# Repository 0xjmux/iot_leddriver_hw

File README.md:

# Spotify Neopixel Visualizer Hardware
Simple and compact ESP32-based WS2812B LED Strip Driver.   

<!-- * Board firmware (in progress, not yet published) will be eventually available at [iot_leddriver_sw](https://github.com/0xjmux/iot_leddriver_sw). -->
* Origianlly planned to design my own firmware to integrate with the Spotify API Directly; but eventually switched to the much more featured combination of WLED + LEDFx. 
* Compatible with the popular [WLED](https://github.com/Aircoookie/WLED) firmware: just change the LED data pin to `GPIO21`. 
* (See [DEVELOPMENT-NOTES.md](DEVELOPMENT-NOTES.md) for full pinout and other information).

> [!WARNING]
> This was my first real PCB design, and I've improved a lot since I completed it. Take it (especially <=v2.2) with a grain of salt. 
 
### Features
* ESP32 based for low-cost IoT Capability, can use either `ESP32-S2-SOLO` (single core, cheaper) or `ESP32-S3-WROOM` (dual core). 
* Programmable over USB C, with Tag-Connect JTAG header for full debug capability. 
* Two ways to attach LED strip, either via pin header or with a strain relief. 
* Board designed to drive a 5m 60LED/m WS2812B strip with safety marign (see [DEVELOPMENT-NOTES.md](DEVELOPMENT-NOTES.md))
* Entirely LCSC BOM, designed for both hand and machine assembly. Able to be assembled by JLCPCB with low-cost components (almost all basic component BOM).

##### Optional Features and Mounting
* Designed to also be capable of driving 12V strips like the WS2811; only modification needed is changing the 5V overvoltage protection diodes (`D1`&`D2`, PN `SMF5V0A`) to 12V diodes (like `SMF12A`s)
* M2 mounting holes, various test pads, and an emergency UART header on the bottom. 
* Includes I2C breakout for optional addition of SSD1306 OLED.
* MEMS Microphone can optionally be added for live sound reactivity. 

#### Update 1/2024 - Now with a 3D Printable case!
* Check out [case/](./case/) for the 3D printable case I designed! This is the result of my first design using CAD in a very long time, and while it has some things I would change now I think it's still probably better published than not. 
* A PDF drawing of the case with dimensions can be found [here](case/iot_leddriver_drawing_v0.5.pdf).

## Notes and Usage
* Schematic, BOM, Gerbers, and all other files needed for production and assembly can be found attached to the latest [release!](https://github.com/0xjmux/iot_leddriver_hw/releases/latest)
  * This includes an interactive HTML BOM, which makes hand assembly much easier. 
* View current layout and schematic live on [KiCanvas](https://kicanvas.org/?github=https%3A%2F%2Fgithub.com%2F0xjmux%2Fiot_leddriver_hw%2Ftree%2Fmain%2FPCB)

<p align="center">
  
<br>v2.1 showing LED strip standard JST connector connected to 5M WS2812B strip
</p>

## Versions
### V2.2 - QoL and Improvements for Production
* Mostly minor updates, to bring the board up to a more "production" ready state. Some modifications/fixes for small things found during manual assembly. 
* Power trace width from USB C port increased so short lengths of strip can be driven directly from USB.
* Traces cleaned up, PWR_LED can now be disconnected (if it's going to be deployed somewhere and the constant light is unwanted). USB_PWR jumpers removed. 
* BOM consolidation, some notes added to schematic, documentation improvements. 

### V2.1 - Hand Assembleable
* MCU originally selected for V2, the `ESP32-S2-MINI`, wasn't hand assemble-able; so it's been replaced with an `ESP32-S2-SOLO`. 
* Various small upgrades, including removal of non-necessary RC components, a mini UART header, and additional 5V power lines right next to the 2.1mm jack for strips with additional power wires. 
* The footprint and supporting components for a MEMS Microphone (`SPH0641LM4H-1`) added in case live sound reactivity is desired later on. 

### V2.0 - Complete redesign, now ESP32 Based
* Board upgraded to the `ESP32-S2-MINI-2-N4` for better compute capability, completely redesigned solely around the WS2812B.
* Most of the features listed above were introduced in this version.

---
### V1.0 Prototype
* [Link to v1.0 branch](https://github.com/0xjmux/iot_leddriver_hw/tree/v1.0)
* V1.0 was an IoT enabled LED strip driver using ESP8266 capable of using both WS2812B (Neopixel) and standard 5050 12V LED strips. Goal is to integrate with the spotify API to allow color changes in reaction to music. 
* V1 was never fully tested; right as v1.0 was ready my goal with the project shifted, and the ESP82666 just doesn't have enough compute for what I wanted to do. 
* If board will only be used in 5V (neopixel) mode, then the 3 `UMW30N06` Mosfets and 2 of the `MCP1416` mosfet drivers are not needed. Additionally, if the board will only be run in one mode then the unused 2.1mm jack does not need to be installed.

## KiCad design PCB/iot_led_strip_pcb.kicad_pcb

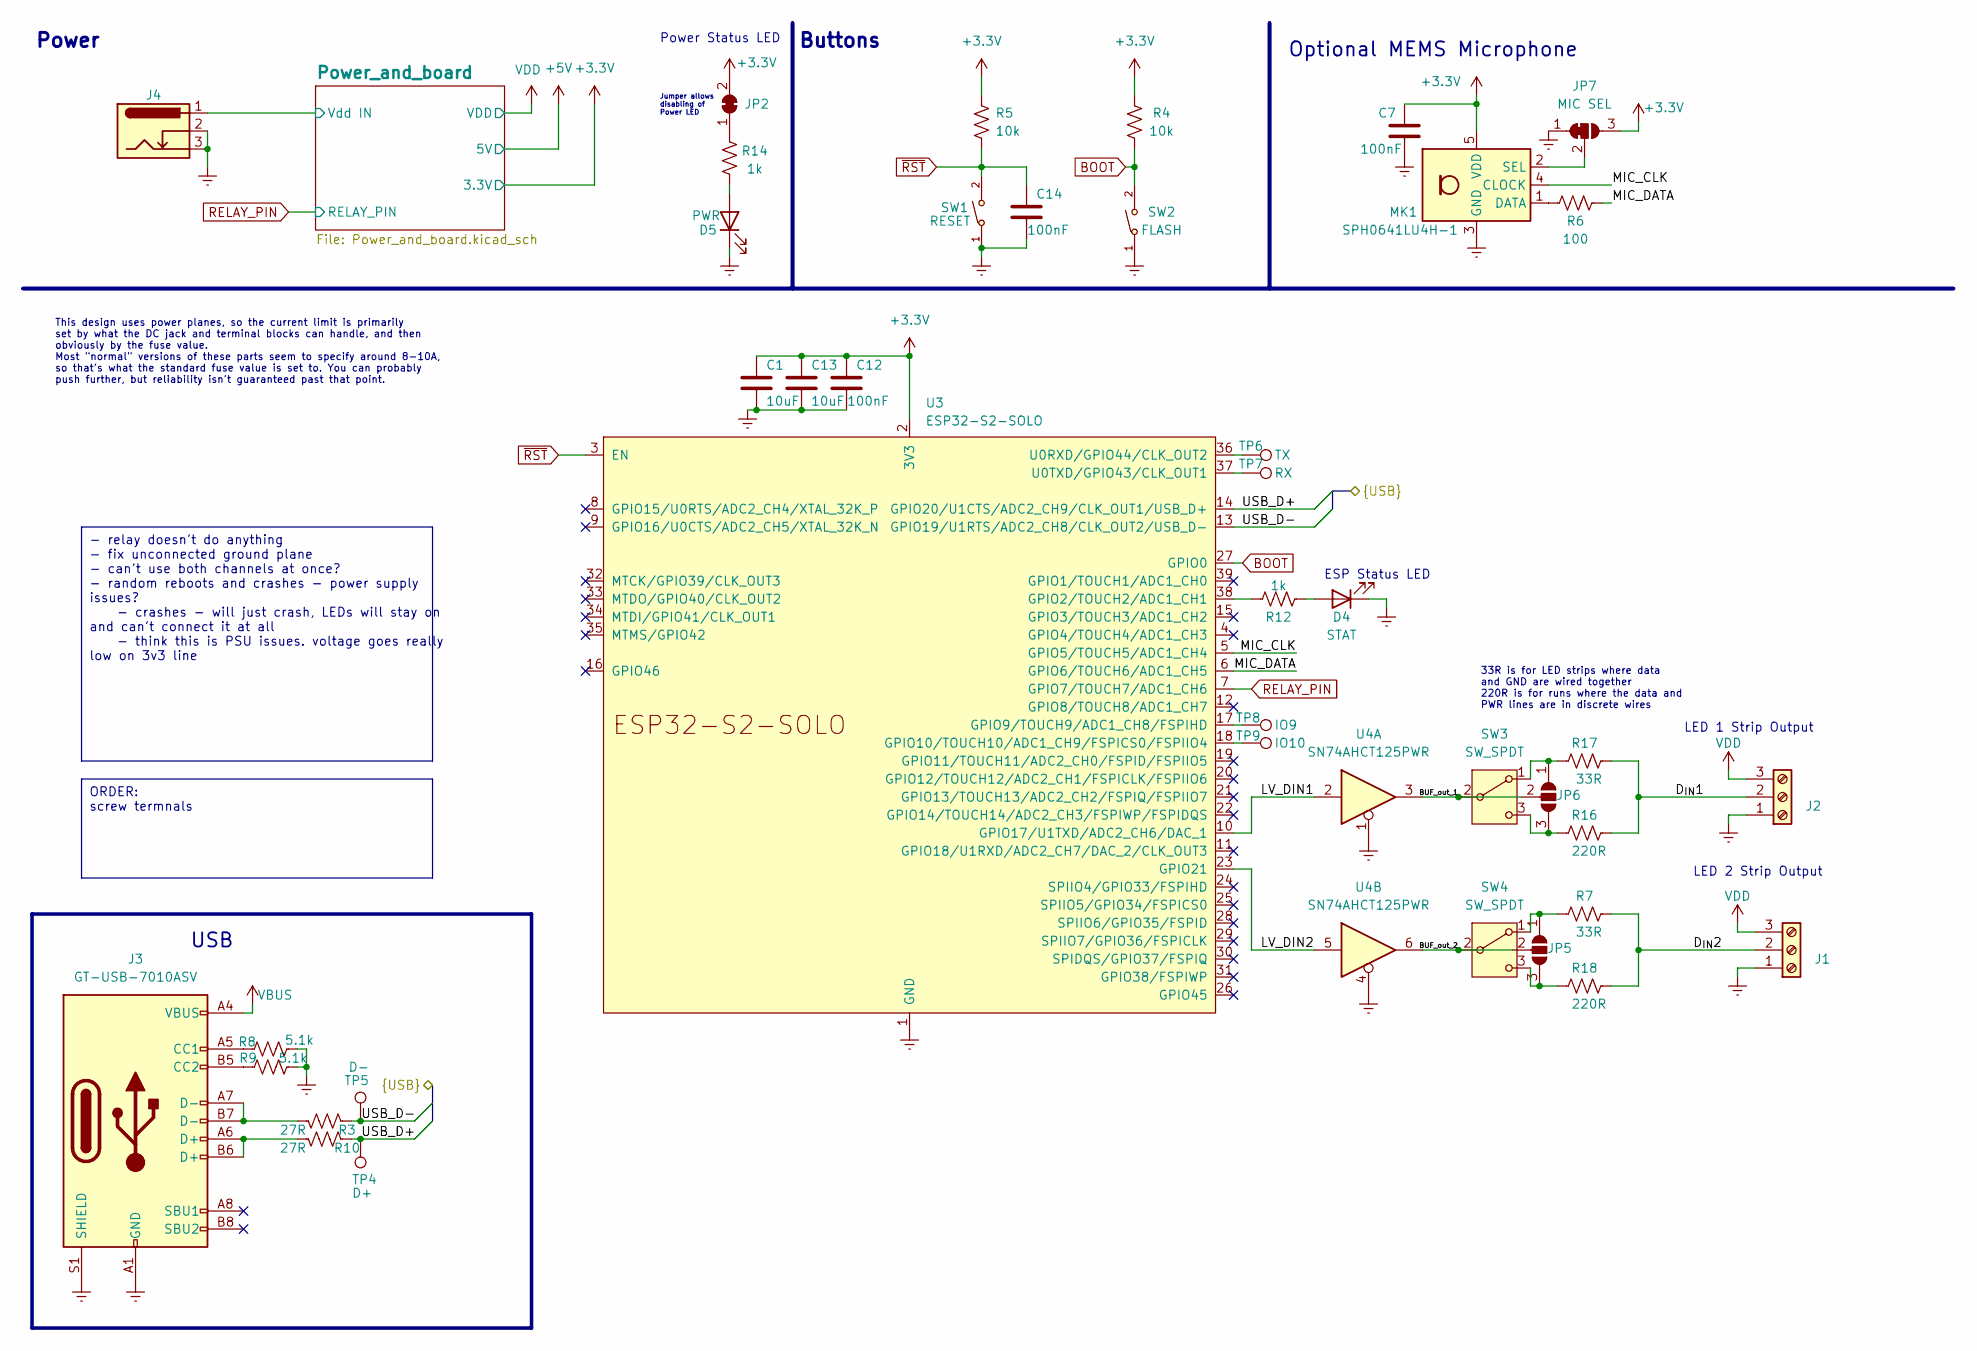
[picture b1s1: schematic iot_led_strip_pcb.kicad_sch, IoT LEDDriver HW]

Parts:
C1, C13: 10uF; C_0805_2012Metric_Pad1.18x1.45mm_HandSolder; LCSC C15850
C7, C12, C14: 100nF; C_0805_2012Metric_Pad1.18x1.45mm_HandSolder; LCSC C49678
D4: STAT; LED_0805_2012Metric_Pad1.15x1.40mm_HandSolder; LCSC C2297
D5: PWR; LED_0805_2012Metric_Pad1.15x1.40mm_HandSolder; LCSC C84256
J1, J2: Screw_Terminal_01x03; TerminalBlock_bornier-3_P5.08mm; LCSC C5188425
J3: GT-USB-7010ASV; USB-C-GT7010_FIXED; LCSC C2988369
J4: Barrel_Jack_Switch_Pin3Ring; BarrelJack_Wuerth_6941xx301002
JP2: PWR_LED_BRIDGE; SolderJumper-2_P1.3mm_Bridged_RoundedPad1.0x1.5mm
JP5, JP6: SolderJumper_3_Open; SolderJumper-3_P1.3mm_Open_Pad1.0x1.5mm
JP7: MIC SEL; SolderJumper-3_P1.3mm_Bridged12_RoundedPad1.0x1.5mm
MK1: SPH0641LU4H-1; Knowles_LGA-5_3.5x2.65mm; LCSC C5454543
R3, R10: 27R; R_0805_2012Metric_Pad1.20x1.40mm_HandSolder; LCSC C17594
R4, R5: 10k; R_0805_2012Metric_Pad1.20x1.40mm_HandSolder; LCSC C17414
R6: 100; R_0805_2012Metric_Pad1.20x1.40mm_HandSolder; LCSC C17408
R7, R17: 33R; R_0805_2012Metric_Pad1.20x1.40mm_HandSolder; LCSC C17634
R8, R9: 5.1k; R_0805_2012Metric_Pad1.20x1.40mm_HandSolder; LCSC C27834
R12, R14: 1k; R_0805_2012Metric_Pad1.20x1.40mm_HandSolder; LCSC C17513
R16, R18: 220R; R_0805_2012Metric_Pad1.20x1.40mm_HandSolder; LCSC C17557
SW1: RESET; SW_SPST_TL3342; LCSC C318884
SW2: FLASH; SW_SPST_TL3342; LCSC C318884
SW3, SW4: SW_SPDT; SW_SPDT_PCM12; LCSC C319020
TP4: D+; TestPoint_Pad_D1.5mm
TP5: D-; TestPoint_Pad_D1.5mm
TP6: TX; TestPoint_Pad_D1.5mm
TP7: RX; TestPoint_Pad_D1.5mm
TP8: IO9; TestPoint_Pad_D1.5mm
TP9: IO10; TestPoint_Pad_D1.5mm
U3: ESP32-S2-SOLO; LCSC C3040594
U4: SN74AHCT125PWR; TSSOP-14_4.4x5mm_P0.65mm; LCSC C36365

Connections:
+3.3V: C1.1, C7.1, C12.1, C13.1, JP2.2 (B), JP7.3 (B), MK1.5 (VDD), R4.2, R5.1, U3.2 (3V3); also elsewhere on the board
/BUF_out_1: JP6.2 (C), SW3.2 (B), U4.3
/BUF_out_2: JP5.2 (C), SW4.2 (B), U4.6
/D_{IN}1: J2.2, R16.2, R17.2
/D_{IN}2: J1.2, R7.2, R18.2
/LV_DIN1: U3.10 (GPIO17/U1TXD/ADC2_CH6/DAC_1), U4.2
/LV_DIN2: U3.23 (GPIO21), U4.5
/MIC_CLK: MK1.4 (CLOCK), U3.5 (GPIO5/TOUCH5/ADC1_CH4)
/MIC_DATA: R6.1, U3.6 (GPIO6/TOUCH6/ADC1_CH5)
/Power_and_board/Vdd IN: J4.1; also elsewhere on the board
/USB_D+: R10.2, TP4.1, U3.14 (GPIO20/U1CTS/ADC2_CH9/CLK_OUT1/USB_D+)
/USB_D-: R3.2, TP5.1, U3.13 (GPIO19/U1RTS/ADC2_CH8/CLK_OUT2/USB_D-)
BOOT: R4.1, SW2.2, U3.27 (GPIO0)
Earth: C1.2, C7.2, C12.2, C13.2, C14.2, D4.1 (K), D5.1 (K), J1.1, J2.1, J3.A1 (GND), J3.A12 (GND), J3.B1 (GND), J3.B12 (GND), J3.S1 (SHIELD), J4.2, J4.3, JP7.1 (A), MK1.3 (GND), R8.2, R9.1, SW1.1, SW2.1, U3.1 (GND), U3.40 (GND), U3.41 (GND), U4.1, U4.4; also elsewhere on the board
unnamed: D4.2 (A), R12.1
unnamed: D5.2 (A), R14.1
unnamed: J3.A5 (CC1), R8.1
unnamed: J3.B5 (CC2), R9.2
unnamed: J3.A6 (D+), J3.B6 (D+), R10.1
unnamed: J3.A7 (D-), J3.B7 (D-), R3.1
unnamed: JP2.1 (A), R14.2
unnamed: JP5.1 (A), R7.1, SW4.1 (A)
unnamed: JP5.3 (B), R18.1, SW4.3 (C)
unnamed: JP6.1 (A), R17.1, SW3.1 (A)
unnamed: JP6.3 (B), R16.1, SW3.3 (C)
unnamed: JP7.2 (C), MK1.2 (SEL)
unnamed: MK1.1 (DATA), R6.2
unnamed: R12.2, U3.38 (GPIO2/TOUCH2/ADC1_CH1)
unnamed: TP8.1, U3.17 (GPIO9/TOUCH9/ADC1_CH8/FSPIHD)
unnamed: TP9.1, U3.18 (GPIO10/TOUCH10/ADC1_CH9/FSPICS0/FSPIIO4)
unnamed: TP6.1, U3.36 (U0RXD/GPIO44/CLK_OUT2)
unnamed: TP7.1, U3.37 (U0TXD/GPIO43/CLK_OUT1)
RELAY_PIN: U3.7 (GPIO7/TOUCH7/ADC1_CH6); also elsewhere on the board
VBUS: J3.A4 (VBUS), J3.A9 (VBUS), J3.B4 (VBUS), J3.B9 (VBUS); also elsewhere on the board
VDD: J1.3, J2.3; also elsewhere on the board
~RST: C14.1, R5.2, SW1.2, U3.3 (EN)

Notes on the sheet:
ORDER: screw termnals
- relay doesn't do anything - fix unconnected ground plane - can't use both channels at once? - random reboots and crashes - power supply issues? - crashes - will just crash, LEDs will stay on and can't connect it at all - think this is PSU issues. voltage goes really low on 3v3 line
Power
Buttons
Jumper allows disabling of Power LED
33R is for LED strips where data and GND are wired together 220R is for runs where the data and PWR lines are in discrete wires
This design uses power planes, so the current limit is primarily set by what the DC jack and terminal blocks can handle, and then obviously by the fuse value. Most "normal" versions of these parts seem to specify around 8-10A, so that's what the standard fuse value is set to. You can probably push 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
LED 2 Strip Output
LED 1 Strip Output
ESP Status LED
Power Status LED
USB
Optional MEMS Microphone

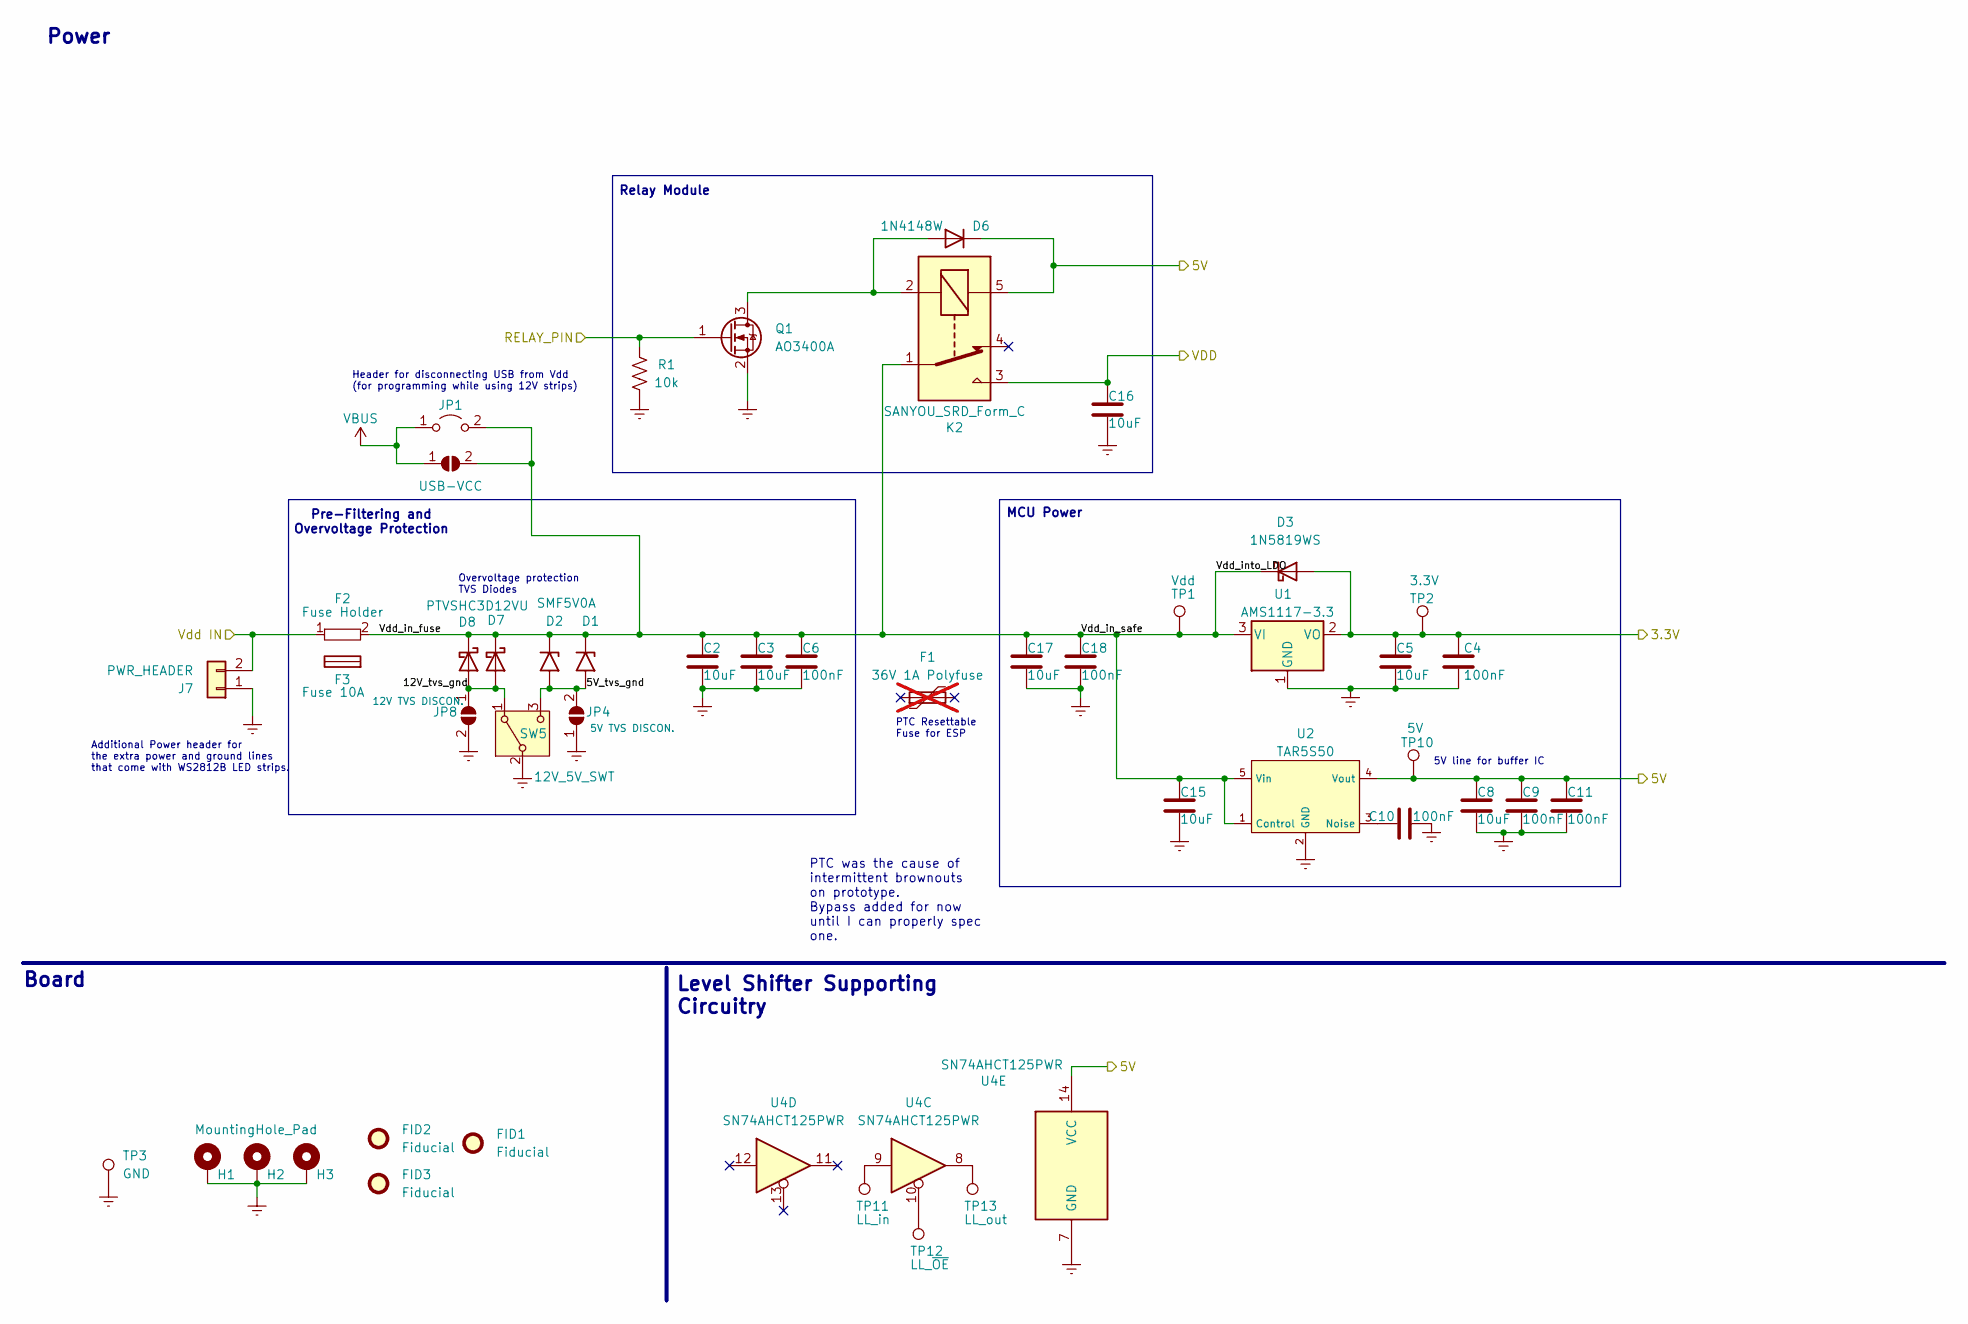
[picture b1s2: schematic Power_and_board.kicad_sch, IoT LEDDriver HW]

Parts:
C2, C3, C5, C8, C15, C16, C17: 10uF; C_0805_2012Metric_Pad1.18x1.45mm_HandSolder; LCSC C15850
C4, C6, C9, C10, C11, C18: 100nF; C_0805_2012Metric_Pad1.18x1.45mm_HandSolder; LCSC C49678
D1, D2: SMF5V0A; D_SMF; LCSC C1972946
D3: 1N5819WS; D_SOD-323_HandSoldering; LCSC C191023
D6: 1N4148W; D_SOD-123; LCSC C81598
D7, D8: PTVSHC3D12VU; D_SOD-323_HandSoldering; LCSC C169336
F1: 36V 1A Polyfuse; Fuse_1206_3216Metric_Pad1.42x1.75mm_HandSolder; LCSC C20616702; not fitted
F2: Fuse Holder; FUSE-TH_XF-505P; LCSC C843270
F3: Fuse 10A
FID1, FID2, FID3: Fiducial; Fiducial_0.5mm_Mask1mm
H1, H2, H3: MountingHole_Pad; MountingHole_2.2mm_M2_Pad_Via
J7: PWR_HEADER; SolderWire-0.5sqmm_1x02_P4.6mm_D0.9mm_OD2.1mm
JP1: USB-VDD; TestPoint_2Pads_Pitch2.54mm_Drill0.8mm
JP3: USB-VCC; SolderJumper-2_P1.3mm_Open_RoundedPad1.0x1.5mm
JP4: 5V TVS DISCON.; SolderJumper-2_P1.3mm_Open_RoundedPad1.0x1.5mm
JP8: 12V TVS DISCON.; SolderJumper-2_P1.3mm_Open_RoundedPad1.0x1.5mm
K2: SANYOU_SRD_Form_C; Relay_SPDT_SANYOU_SRD_Series_Form_C; LCSC C35449
Q1: AO3400A; SOT-23_Handsoldering; LCSC C20917
R1: 10k; R_0805_2012Metric_Pad1.20x1.40mm_HandSolder; LCSC C17414
SW5: 12V_5V_SWT; SW_SPDT_PCM12; LCSC C319020
TP1: Vdd; TestPoint_Pad_D1.5mm
TP2: 3.3V; TestPoint_Pad_D1.5mm
TP3: GND; TestPoint_Pad_D1.5mm
TP10: 5V; TestPoint_Pad_D1.5mm
TP11: LL_in; TestPoint_Pad_D1.0mm
TP12: LL_~{OE}; TestPoint_Pad_D1.0mm
TP13: LL_out; TestPoint_Pad_D1.0mm
U1: AMS1117-3.3; SOT-223-3_TabPin2; LCSC C6186
U2: TAR5S50; SSOP-5_L2.9-W1.6-P0.95-LS2.8-TL; LCSC C146354
U4: SN74AHCT125PWR; TSSOP-14_4.4x5mm_P0.65mm; LCSC C36365

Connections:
+3.3V: C4.1, C5.1, D3.2 (A), TP2.1, U1.2 (VO); also elsewhere on the board
+5V: C8.1, C9.1, C11.1, D6.1 (K), K2.5, TP10.1, U2.4 (Vout), U4.14 (VCC)
/Power_and_board/5V_tvs_gnd: D1.2 (A2), D2.2 (A2), JP4.2 (B), SW5.3 (C)
/Power_and_board/12V_tvs_gnd: D7.2 (A), D8.2 (A), JP8.1 (A), SW5.1 (A)
/Power_and_board/Vdd IN: F2.1, J7.2; also elsewhere on the board
/Power_and_board/Vdd_in_fuse: C2.1, C3.1, C6.1, C15.1, C17.1, C18.1, D1.1 (A1), D2.1 (A1), D3.1 (K), D7.1 (K), D8.1 (K), F2.2, JP1.2 (B), JP3.2 (B), K2.1, TP1.1, U1.3 (VI), U2.1 (Control), U2.5 (Vin)
Earth: C2.2, C3.2, C4.2, C5.2, C6.2, C8.2, C9.2, C10.2, C11.2, C15.2, C16.2, C17.2, C18.2, H1.1, H2.1, H3.1, J7.1, JP4.1 (A), JP8.2 (B), Q1.2 (S), R1.1, SW5.2 (B), TP3.1, U1.1 (GND), U2.2 (GND), U4.7 (GND); also elsewhere on the board
unnamed: D6.2 (A), K2.2, Q1.3 (D)
unnamed: TP11.1, U4.9
unnamed: TP12.1, U4.10
unnamed: TP13.1, U4.8
unnamed: C10.1, U2.3 (Noise)
RELAY_PIN: Q1.1 (G), R1.2; also elsewhere on the board
VBUS: JP1.1 (A), JP3.1 (A); also elsewhere on the board
VDD: C16.1, K2.3; also elsewhere on the board

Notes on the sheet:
PTC was the cause of intermittent brownouts on prototype. Bypass added for now until I can properly spec one.
5V line for buffer IC
Overvoltage protection TVS Diodes
Relay Module
MCU Power
Header for disconnecting USB from Vdd (for programming while using 12V strips)
Pre-Filtering and Overvoltage Protection
PTC Resettable Fuse for ESP
Board
Additional Power header for the extra power and ground lines that come with WS2812B LED strips.
Power
Level Shifter Supporting Circuitry

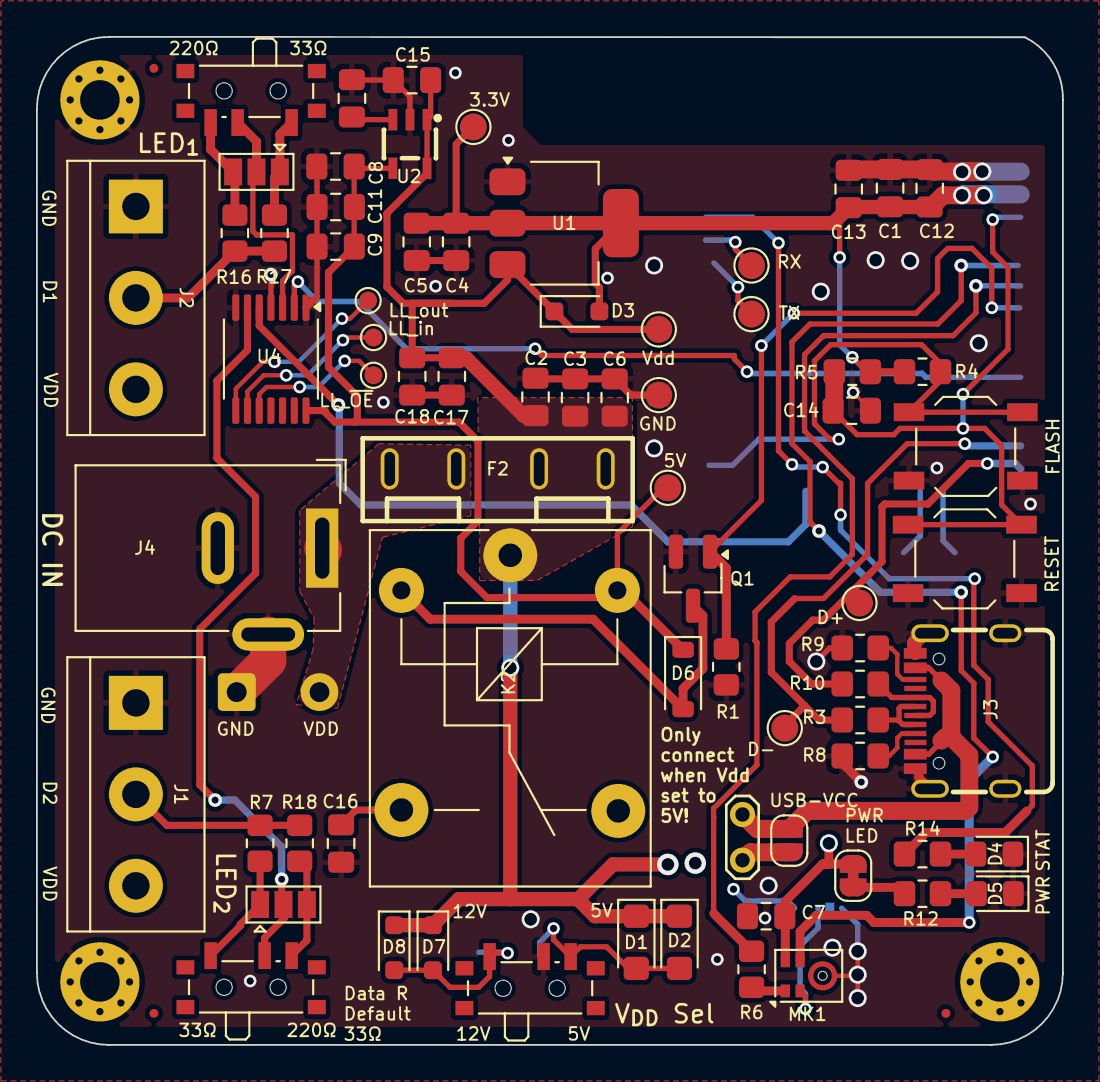
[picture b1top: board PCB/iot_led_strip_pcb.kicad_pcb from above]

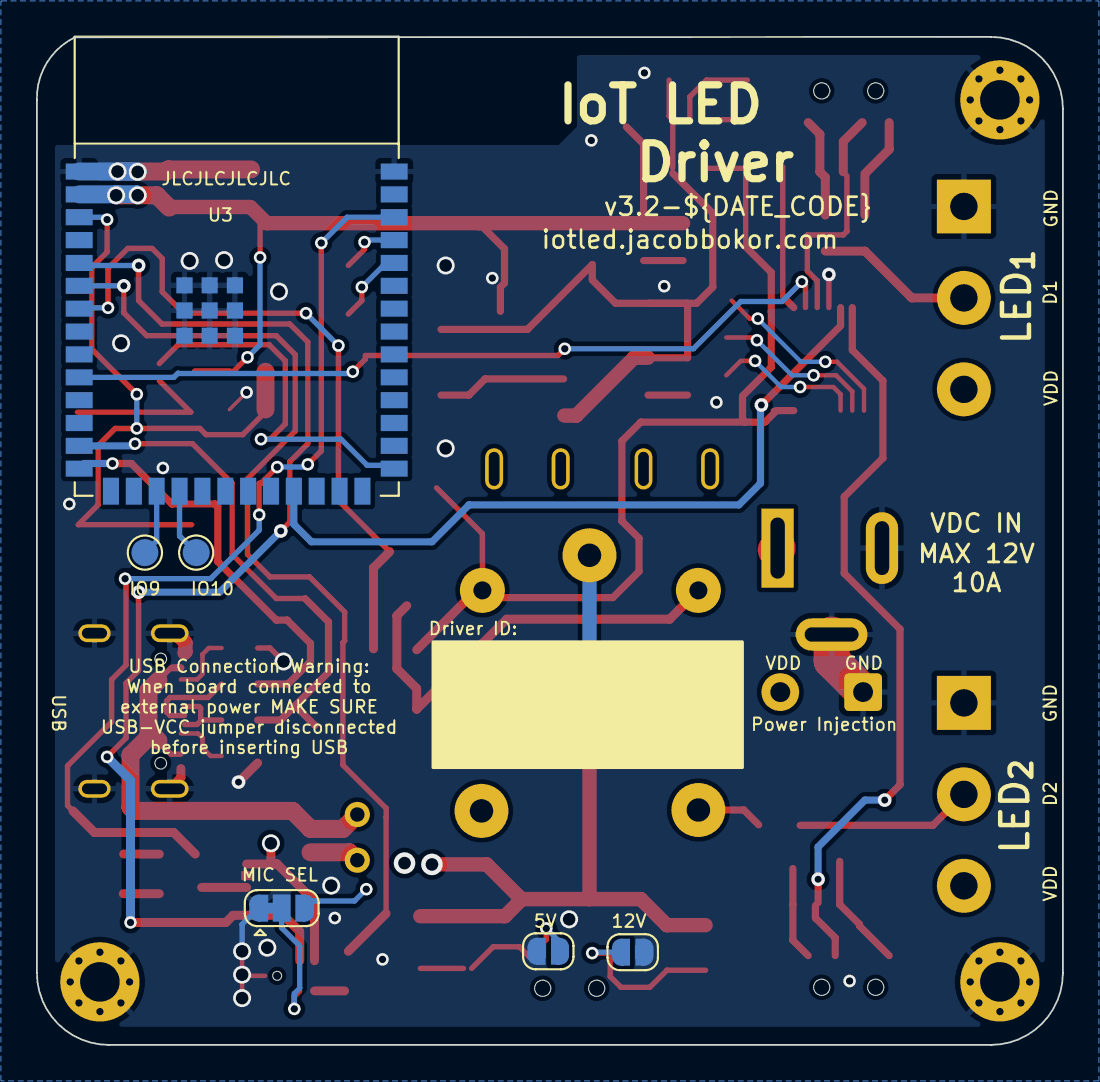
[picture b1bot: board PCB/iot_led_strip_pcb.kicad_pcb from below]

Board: 4 copper layers, 57.0 x 56.0 mm, 85 parts (6 on the bottom side), 45 nets.

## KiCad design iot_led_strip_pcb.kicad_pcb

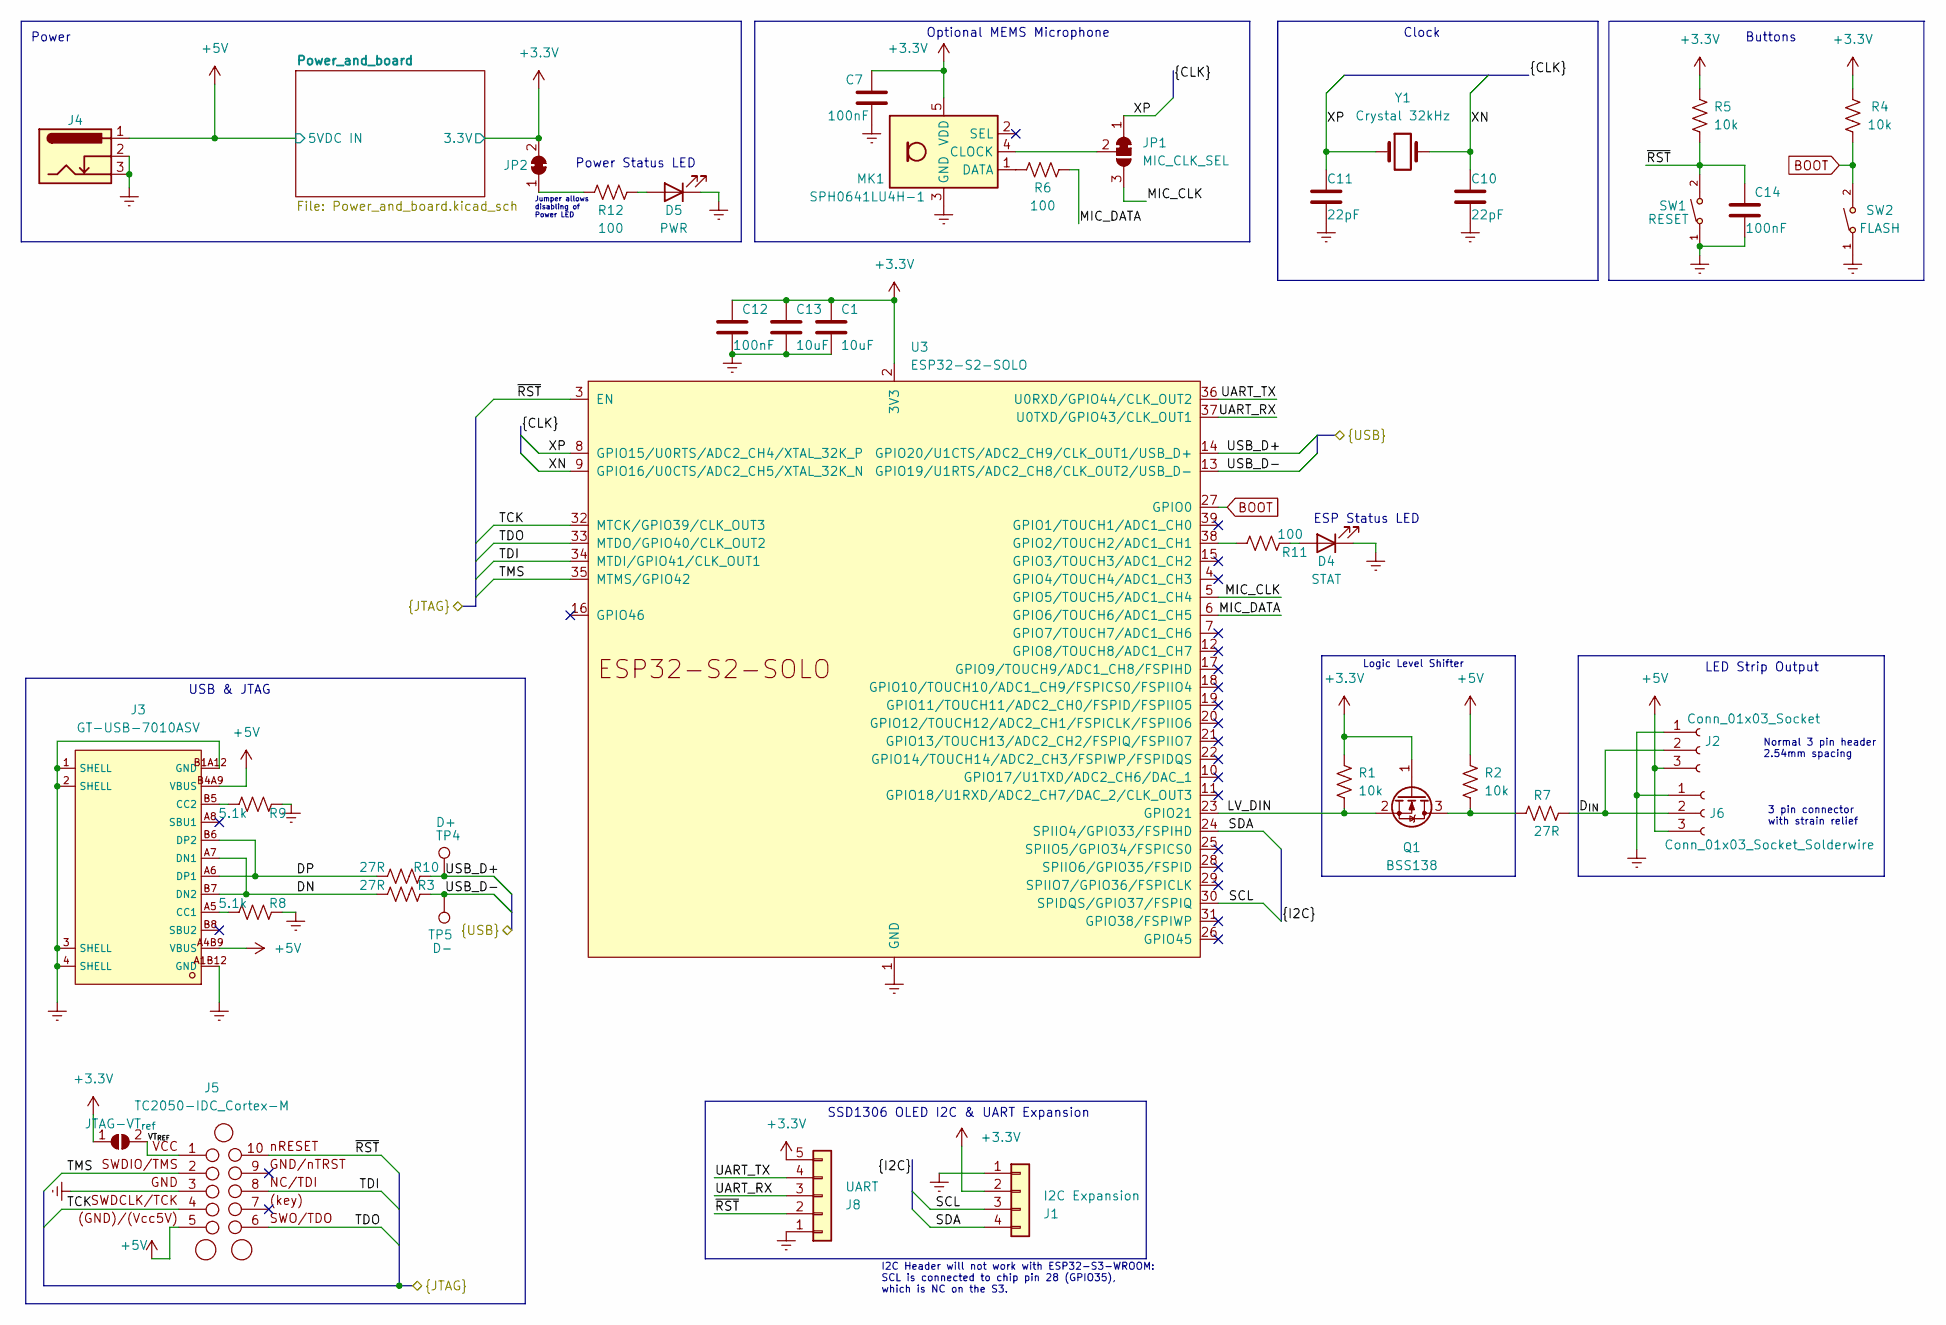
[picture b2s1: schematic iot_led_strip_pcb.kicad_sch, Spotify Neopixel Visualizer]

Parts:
C1, C13: 10uF; C_0805_2012Metric_Pad1.18x1.45mm_HandSolder; LCSC C15850
C7, C12, C14: 100nF; C_0805_2012Metric_Pad1.18x1.45mm_HandSolder; LCSC C49678
C10, C11: 22pF; C_0805_2012Metric_Pad1.18x1.45mm_HandSolder; LCSC C1804
D4: STAT; LED_0805_2012Metric_Pad1.15x1.40mm_HandSolder; LCSC C2297
D5: PWR; LED_0805_2012Metric_Pad1.15x1.40mm_HandSolder; LCSC C84256
J1: I2C Expansion; PinHeader_1x04_P2.54mm_Vertical
J2: Conn_01x03_Socket; PinHeader_1x03_P2.54mm_Vertical
J3: GT-USB-7010ASV; USB-C-SMD_G-SWITCH_GT-USB-7010ASV; LCSC C2988369
J4: Barrel_Jack_Switch_Pin3Ring; BarrelJack_Wuerth_6941xx301002
J5: TC2050-IDC_Cortex-M; Tag-Connect_TC2050-IDC-FP_2x05_P1.27mm_Vertical
J6: Conn_01x03_Socket_Solderwire; SolderWire-0.5sqmm_1x03_P4.6mm_D0.9mm_OD2.1mm_Relief
J8: UART; 5 Pin Pad array
JP1: MIC_CLK_SEL; SolderJumper-3_P1.3mm_Bridged12_RoundedPad1.0x1.5mm
JP2: PWR_LED_BRIDGE; SolderJumper-2_P1.3mm_Bridged_RoundedPad1.0x1.5mm
JP7: JTAG-VT_{ref}; SolderJumper-2_P1.3mm_Open_RoundedPad1.0x1.5mm
MK1: SPH0641LU4H-1; Knowles_LGA-5_3.5x2.65mm; LCSC C5454543
Q1: BSS138; SOT-23; LCSC C358381
R1, R2, R4, R5: 10k; R_0805_2012Metric_Pad1.20x1.40mm_HandSolder; LCSC C17414
R3, R7, R10: 27R; R_0805_2012Metric_Pad1.20x1.40mm_HandSolder; LCSC C17594
R6, R11, R12: 100; R_0805_2012Metric_Pad1.20x1.40mm_HandSolder; LCSC C17408
R8, R9: 5.1k; R_0805_2012Metric_Pad1.20x1.40mm_HandSolder; LCSC C27834
SW1: RESET; SW_SPST_TL3342; LCSC C318884
SW2: FLASH; SW_SPST_TL3342; LCSC C318884
TP4: D+; TestPoint_Pad_D1.0mm
TP5: D-; TestPoint_Pad_D1.0mm
U3: ESP32-S2-SOLO; LCSC C3040594
Y1: Crystal 32kHz; Crystal_SMD_3215-2Pin_3.2x1.5mm; LCSC C97606

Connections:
+3.3V: C1.1, C7.1, C12.1, C13.1, J1.2, J8.5, JP2.2 (B), JP7.1 (A), MK1.5 (VDD), Q1.1 (G), R1.1, R4.2, R5.1, U3.2 (3V3); also elsewhere on the board
+5V: J2.3, J3.A4B9 (VBUS), J3.B4A9 (VBUS), J4.1, J5.5 ((GND)/(Vcc5V)), J6.3, R2.1; also elsewhere on the board
/DN: J3.A7 (DN1), J3.B7 (DN2), R3.1
/DP: J3.A6 (DP1), J3.B6 (DP2), R10.1
/D_{IN}: J2.2, J6.2, R7.2
/LV_DIN: Q1.2 (S), R1.2, U3.23 (GPIO21)
/MIC_CLK: JP1.3 (B), U3.5 (GPIO5/TOUCH5/ADC1_CH4)
/MIC_DATA: R6.1, U3.6 (GPIO6/TOUCH6/ADC1_CH5)
/SCL: J1.3, U3.30 (SPIDQS/GPIO37/FSPIQ)
/SDA: J1.4, U3.24 (SPIIO4/GPIO33/FSPIHD)
/TCK: J5.4 (SWDCLK/TCK), U3.32 (MTCK/GPIO39/CLK_OUT3)
/TDI: J5.8 (NC/TDI), U3.34 (MTDI/GPIO41/CLK_OUT1)
/TDO: J5.6 (SWO/TDO), U3.33 (MTDO/GPIO40/CLK_OUT2)
/TMS: J5.2 (SWDIO/TMS), U3.35 (MTMS/GPIO42)
/UART_RX: J8.3, U3.37 (U0TXD/GPIO43/CLK_OUT1)
/UART_TX: J8.4, U3.36 (U0RXD/GPIO44/CLK_OUT2)
/USB_D+: R10.2, TP4.1, U3.14 (GPIO20/U1CTS/ADC2_CH9/CLK_OUT1/USB_D+)
/USB_D-: R3.2, TP5.1, U3.13 (GPIO19/U1RTS/ADC2_CH8/CLK_OUT2/USB_D-)
/VT_{REF}: J5.1 (VCC), JP7.2 (B)
/XN: C10.1, U3.9 (GPIO16/U0CTS/ADC2_CH5/XTAL_32K_N), Y1.2
/XP: C11.1, JP1.1 (A), U3.8 (GPIO15/U0RTS/ADC2_CH4/XTAL_32K_P), Y1.1
/~RST: C14.1, J5.10 (nRESET), J8.2, R5.2, SW1.2, U3.3 (EN)
BOOT: R4.1, SW2.2, U3.27 (GPIO0)
Earth: C1.2, C7.2, C10.2, C11.2, C12.2, C13.2, C14.2, D4.1 (K), D5.1 (K), J1.1, J2.1, J3.1 (SHELL), J3.2 (SHELL), J3.3 (SHELL), J3.4 (SHELL), J3.A1B12 (GND), J3.B1A12 (GND), J4.2, J4.3, J5.3 (GND), J6.1, J8.1, MK1.3 (GND), R8.2, R9.2, SW1.1, SW2.1, U3.1 (GND), U3.40 (GND), U3.41 (GND); also elsewhere on the board
unnamed: D4.2 (A), R11.1
unnamed: D5.2 (A), R12.1
unnamed: J3.A5 (CC1), R8.1
unnamed: J3.B5 (CC2), R9.1
unnamed: JP1.2 (C), MK1.4 (CLOCK)
unnamed: JP2.1 (A), R12.2
unnamed: MK1.1 (DATA), R6.2
unnamed: Q1.3 (D), R2.2, R7.1
unnamed: R11.2, U3.38 (GPIO2/TOUCH2/ADC1_CH1)

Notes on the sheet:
Power
I2C Header will not work with ESP32-S3-WROOM: SCL is connected to chip pin 28 (GPIO35), which is NC on the S3.
Buttons
SSD1306 OLED I2C & UART Expansion
3 pin connector with strain relief
Clock
Jumper allows disabling of Power LED
Normal 3 pin header 2.54mm spacing
LED Strip Output
Logic Level Shifter
ESP Status LED
Power Status LED
USB & JTAG
Optional MEMS Microphone

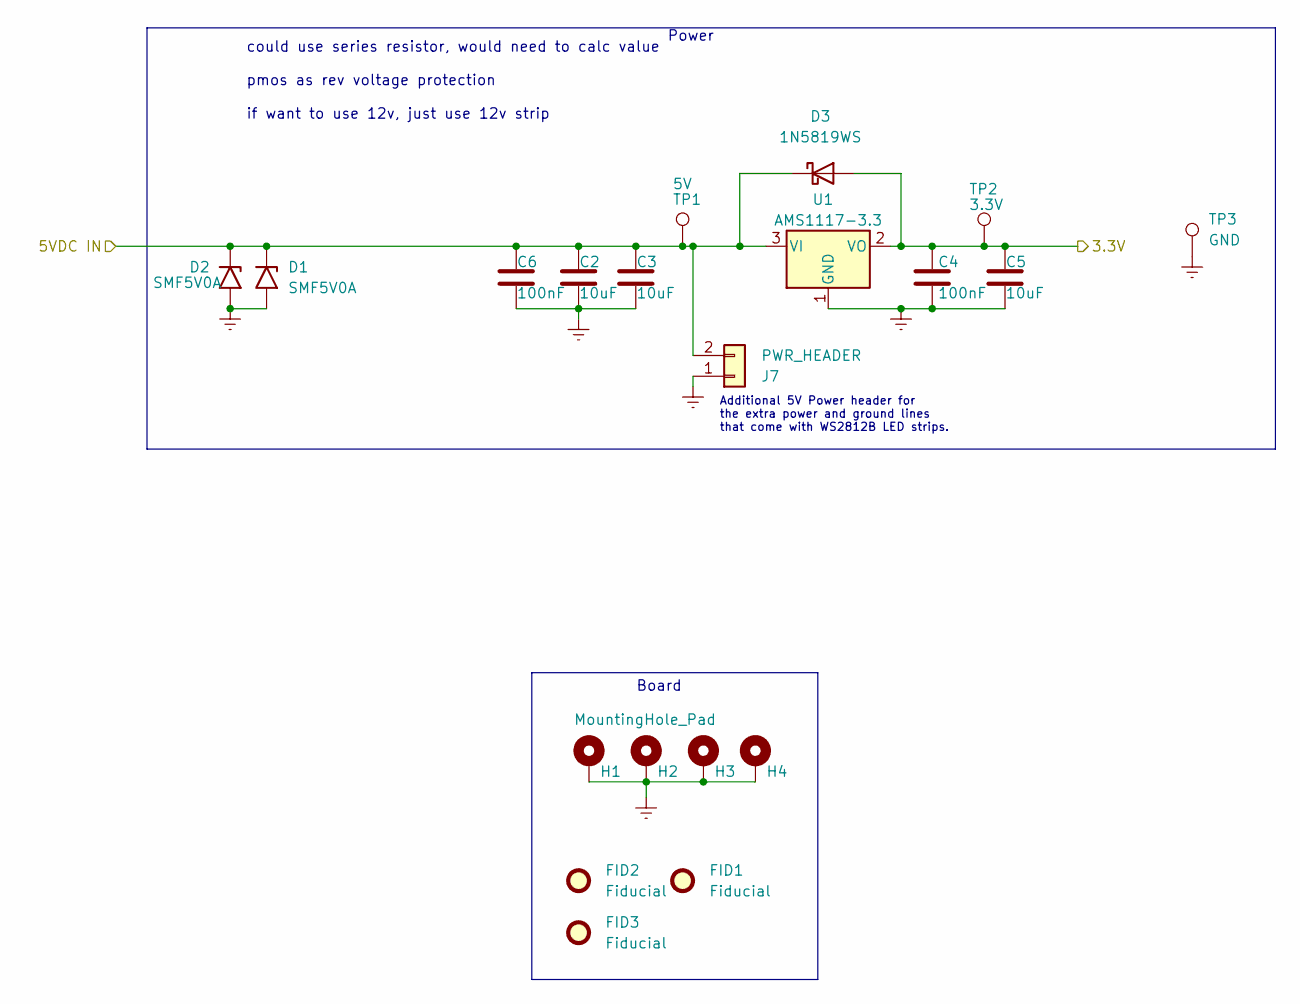
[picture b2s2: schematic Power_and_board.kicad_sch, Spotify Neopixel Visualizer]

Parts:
C2, C3, C5: 10uF; C_0805_2012Metric_Pad1.18x1.45mm_HandSolder; LCSC C15850
C4, C6: 100nF; C_0805_2012Metric_Pad1.18x1.45mm_HandSolder; LCSC C49678
D1, D2: SMF5V0A; D_SMF; LCSC C1972946
D3: 1N5819WS; D_SOD-323_HandSoldering; LCSC C191023
FID1, FID2, FID3: Fiducial; Fiducial_0.5mm_Mask1mm
H1, H2, H3, H4: MountingHole_Pad; MountingHole_2.2mm_M2_Pad_Via
J7: PWR_HEADER; SolderWire-0.1sqmm_1x02_P3.6mm_D0.4mm_OD1mm
TP1: 5V; TestPoint_Pad_D1.5mm
TP2: 3.3V; TestPoint_Pad_D1.5mm
TP3: GND; TestPoint_Pad_D1.5mm
U1: AMS1117-3.3; SOT-223-3_TabPin2; LCSC C6186

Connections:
+3.3V: C4.1, C5.1, D3.2 (A), TP2.1, U1.2 (VO); also elsewhere on the board
+5V: C2.1, C3.1, C6.1, D1.1 (A1), D2.1 (A1), D3.1 (K), J7.2, TP1.1, U1.3 (VI); also elsewhere on the board
Earth: C2.2, C3.2, C4.2, C5.2, C6.2, D1.2 (A2), D2.2 (A2), H1.1, H2.1, H3.1, H4.1, J7.1, TP3.1, U1.1 (GND); also elsewhere on the board

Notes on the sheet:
could use series resistor, would need to calc value pmos as rev voltage protection if want to use 12v, just use 12v strip
Board
Additional 5V Power header for the extra power and ground lines that come with WS2812B LED strips.
Power
